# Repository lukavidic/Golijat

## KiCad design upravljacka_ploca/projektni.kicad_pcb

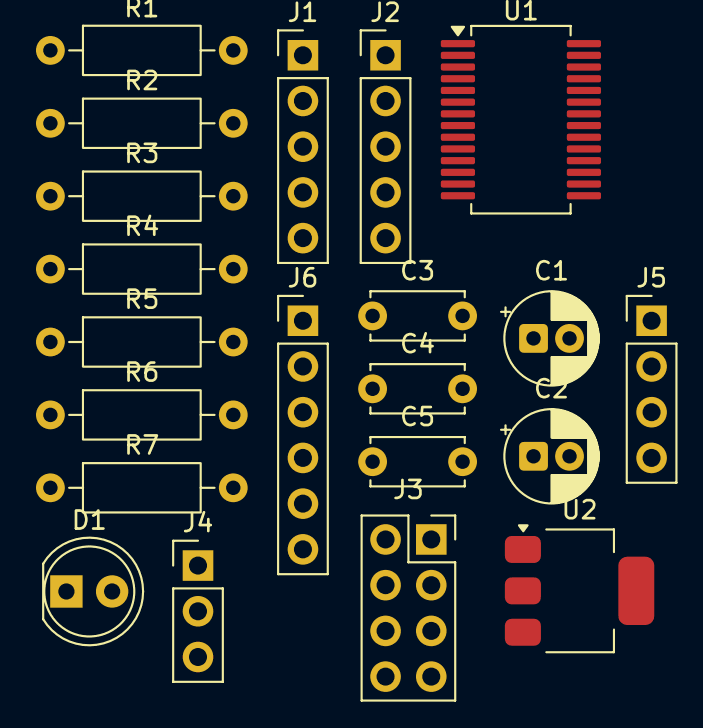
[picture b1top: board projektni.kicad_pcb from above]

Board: 2 copper layers, 21 parts (0 on the bottom side), 22 nets, no tracks yet.

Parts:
C1, C2: 22u; CP_Radial_D5.0mm_P2.00mm
C3, C5: 100n; C_Disc_D5.0mm_W2.5mm_P5.00mm
C4: 10u; C_Disc_D5.0mm_W2.5mm_P5.00mm
D1: LED; LED_D5.0mm
J1, J2: Conn_01x05_Pin; PinHeader_1x05_P2.54mm_Vertical
J3: Conn_02x04_Odd_Even; PinSocket_2x04_P2.54mm_Vertical
J4: Conn_01x03_Pin; PinHeader_1x03_P2.54mm_Vertical
J5: Conn_01x04_Pin; PinHeader_1x04_P2.54mm_Vertical
J6: Conn_01x06_Pin; PinHeader_1x06_P2.54mm_Vertical
R1: 1500; R_Axial_DIN0207_L6.3mm_D2.5mm_P10.16mm_Horizontal
R2, R5: 10k; R_Axial_DIN0207_L6.3mm_D2.5mm_P10.16mm_Horizontal
R3, R4: 4.7k; R_Axial_DIN0207_L6.3mm_D2.5mm_P10.16mm_Horizontal
R6: 1k; R_Axial_DIN0207_L6.3mm_D2.5mm_P10.16mm_Horizontal
R7: 2k; R_Axial_DIN0207_L6.3mm_D2.5mm_P10.16mm_Horizontal
U1: PIC24FJ64GA702-I; pic24fj64ga702-i
U2: AMS1117-3.3; SOT-223-3_TabPin2

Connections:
+3.3V: C2.1, C3.1, C5.2, D1.2 (A), J1.2, J3.8, J4.2, J6.1, R2.2, R3.2, R4.2, R5.1, U1.13 (VDD), U1.28 (AVDD/VDD), U2.2 (VO)
+5V: J2.3, J5.3
+BATT: C1.1, J2.5, U2.3 (VI)
/ECHO: R6.2, R7.1, U1.10 (OSCO/CLKO/C2IND/RA3)
/ESP_RX: J3.7, U1.6 (AN4/C1INB/RP2/SDA2/CTED13/RB2)
/ESP_TX: J3.2, U1.7 (AN5/C1INA/RP3/SCL2/CTED8/RB3)
/IR_AN: J4.1, U1.2 (VREF+/CVREF+/AN0/C3INC/RP26/CTED1/RA0)
/MCLR: J1.1, R2.1, U1.1 (MCLR)
/PGEC1: J1.5, U1.5 (PGC1/AN1-/AN3/C2INA/RP1/CTED12/RB1)
/PGED1: J1.4, U1.4 (PGD1/AN2/CTCMP/C2INB/RP0/RB0)
/RA1: J6.3, U1.3 (VREF-/CVREF-/AN1/C3IND/RP27/CTED2/RA1)
/RB6: J6.4, U1.15 (PGC3/RP6/ASCL1/OCM1F/RB6)
/RB7: J6.5, U1.16 (RP7/OCM1A/CTED3/INT0/RB7)
/RB14: J6.6, U1.25 (CVREF/AN6/C3INB/RP14/CTED5/RB14)
/SCL: J2.2, R4.1, U1.17 (TCK/RP8/SCL1/OCM1B/CTED10/RB8)
/SDA: J2.1, R3.1, U1.18 (TDO/C1INC/C2INC/C3INC/TMPRN/RP9/SDA1/T1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)
/TRIG: J5.1, U1.9 (OSCI/CLKI/C1IND/RA2)
GND: C1.2, C2.2, C3.2, C4.2, C5.1, J1.3, J2.4, J3.1, J4.3, J5.4, J6.2, R1.2, R7.2, U1.8 (VSS), U1.19 (VSS), U1.27 (AVSS/VSS), U2.1 (GND)
unnamed: D1.1 (K), R1.1
unnamed: J3.4, R5.2
unnamed: J5.2, R6.1
unnamed: C4.1, U1.20 (VCAP)
